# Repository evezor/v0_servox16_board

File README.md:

# Servo x16 Board
*please note this board has been deprecated.

This board uses the Evezor Stamp STMF405 MCU

source: https://github.com/evezor/Evezor-Stamp-STMF405

An edge board containing a PCA9685 driver chip capable of controlling 16 servos or LEDs. The board also contains 2 pushbuttons and a dpad for easy control/ debugging. 
Servo power must be supplied from external source

source files can be found here: https://github.com/evezor/v0_servox16_board

Evezor® and all associated marks, logos, and designs are registered trademarks and protected by copyright. Unauthorized use or reproduction of these trademarks and copyrighted materials is strictly prohibited.

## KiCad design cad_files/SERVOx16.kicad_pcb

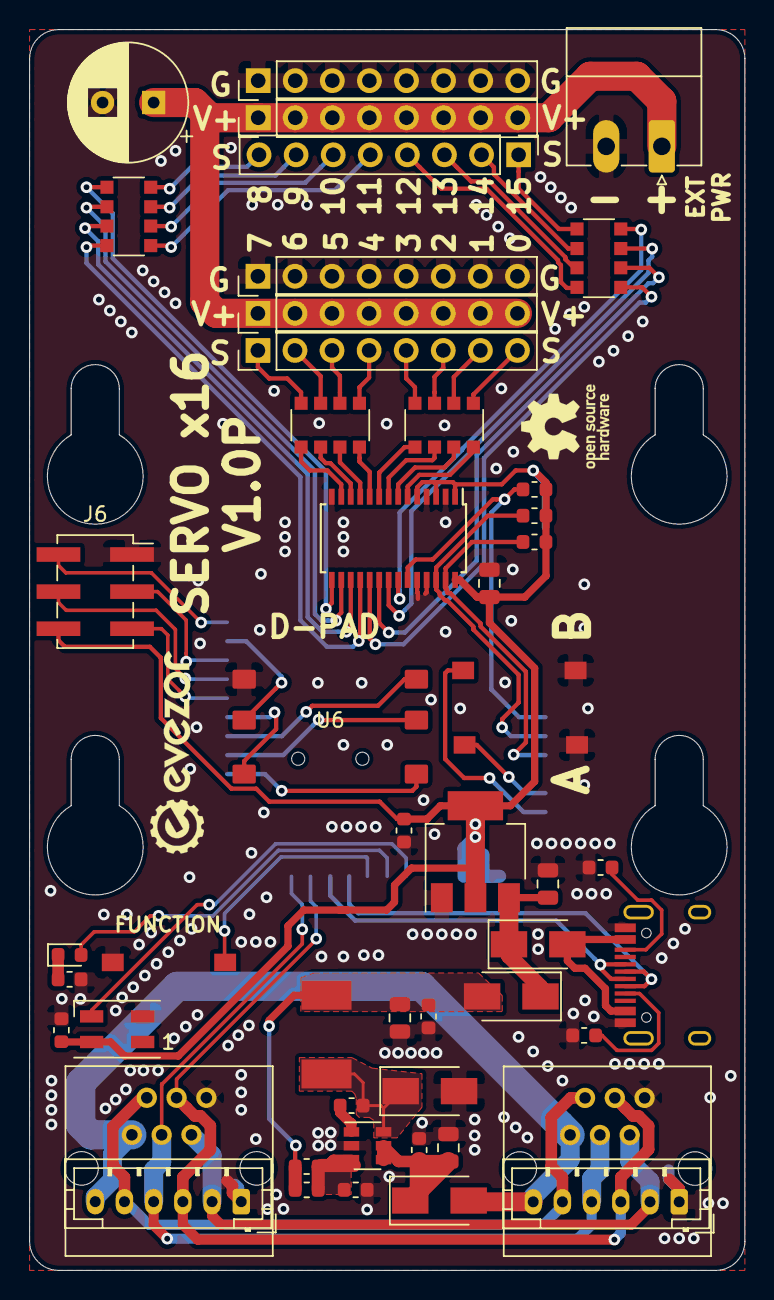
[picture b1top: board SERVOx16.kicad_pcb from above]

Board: 2 copper layers, 49.0 x 85.0 mm, 51 parts (1 on the bottom side), 69 nets.

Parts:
C1, C2, C3, C5, C10: .1uF; C_0603_1608Metric
C4: 4.7uF; C_0805_2012Metric
C6: 22uF; C_0805_2012Metric
C8, C11: 10uF; C_0805_2012Metric
C9: C_Small; C_0603_1608Metric
C12: CP; CP_Radial_D8.0mm_P3.50mm
D1, D2, D4, D5: SX35_SCHOTTKY; D_SMA
D3: LED; LED_0603_1608Metric
D6: SK6812MINI; LED_SK6812MINI_PLCC4_3.5x3.5mm_P1.75mm
J1: USB_C_Receptacle_USB2.0; USB_C_Receptacle_HRO_TYPE-C-31-M-12
J2, J3: RJ11; RJ11_C189747_Horizontal
J4, J5: PH; JST_PH_B6B-PH-K_1x06_P2.00mm_Vertical
J6: Conn_02x03_Odd_Even; PinSocket_2x03_P2.54mm_Vertical_SMD
J7: Conn_01x02; PhoenixContact_MC_1,5_2-G-3.81_1x02_P3.81mm_Horizontal
J8, J9, J10, J11, J12, J13: Conn_01x08; PinHeader_1x08_P2.54mm_Vertical
L1: 22uH; INDUCTOR_7.5X6.6_GCDA0630-220MC
R1, R5: 15k; R_0603_1608Metric
R2: 82k; R_0603_1608Metric
R3, R4: 5.1k; R_0603_1608Metric
R8: 10k; R_0603_1608Metric
R9, R10: 4.7k; R_0603_1608Metric
RN1, RN2, RN3: R_Pack04; R_Array_Convex_4x1206
RN4: 220x4; R_Array_Convex_4x1206
SW1, SW2, SW3: SW_Push; SWITCH_2x3_SMD_TACTILE_GREEN
U1: SY8401ABC; SOT-23-6
U2: AMS1117-3.3; SOT-223-3_TabPin2
U3: EDGE_STM32F405_CPU_V1; EDGE_STAMP
U5: PCA9685PW; TSSOP-28_4.4x9.7mm_P0.65mm
U6: SWITCH_5-WAY_TACTIL_10X10; SWITCH_5WAY_10x10

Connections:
+3V3: C9.2, C10.1, C11.1, D6.4, J6.6, R8.1, R9.1, R10.1, U2.2, U3.1, U3.18, U5.1, U5.3, U5.5, U5.28
/BOOT: J6.3, U3.36
/BUTTON_A: SW3.1, U3.15
/BUTTON_B: SW2.1, U3.16
/CAN_H: J2.3, J3.3, J4.3, J5.3, U3.26
/CAN_L: J2.4, J3.4, J4.4, J5.4, U3.27
/CC1: J1.A5, R4.1
/CC2: J1.B5, R3.1
/D+: J1.A6, J1.B6, U3.25
/D-: J1.A7, J1.B7, U3.24
/DOWN: U3.30, U6.6
/FD_H: J2.2, J3.2, J4.2, J5.2
/FD_L: J2.5, J3.5, J4.5, J5.5
/FUNCTION_BUTTON: SW1.1, U3.23
/HBT_LED: D3.2, U3.22
/LEFT: U3.37, U6.2
/NEO_STATUS: D6.3, U3.21
/OE: R8.2, U3.11, U5.23
/OUTPUT_0: J12.8, RN1.1
/OUTPUT_1: J12.7, RN1.2
/OUTPUT_2: J12.6, RN1.3
/OUTPUT_3: J12.5, RN1.4
/OUTPUT_4: J12.4, RN2.1
/OUTPUT_5: J12.3, RN2.2
/OUTPUT_6: J12.2, RN2.3
/OUTPUT_7: J12.1, RN2.4
/OUTPUT_8: J8.8, RN3.8
/OUTPUT_9: J8.7, RN3.7
/OUTPUT_10: J8.6, RN3.6
/OUTPUT_11: J8.5, RN3.5
/OUTPUT_12: J8.4, RN4.8
/OUTPUT_13: J8.3, RN4.7
/OUTPUT_14: J8.2, RN4.6
/OUTPUT_15: J8.1, RN4.5
/PUSH: U3.33, U6.3
/RESET: J6.2, U3.38
/RIGHT: U3.31, U6.5
/SCL: R10.2, U3.12, U5.26
/SDA: R9.2, U3.13, U5.27
/SLEEVE_SCL: J6.5, U3.34
/SLEEVE_SDA: J6.4, U3.35
/UP: U3.32, U6.4
/USB_VCC: D4.2, J1.A4, J1.A9, J1.B4, J1.B9
/VREG_OUT: C2.1, C5.1, C6.1, D5.2, L1.2, R2.1
GND: C3.2, C4.2, C5.2, C6.2, C8.2, C9.1, C10.2, C11.2, C12.2, D1.2, D6.2, J1.A1, J1.A12, J1.B1, J1.B12, J2.1, J3.1, J4.1, J5.1, J6.1, J7.2, J9.1, J9.2, J9.3, J9.4, J9.5, J9.6, J9.7, J9.8, J11.1, J11.2, J11.3, J11.4, J11.5, J11.6, J11.7, J11.8, R1.1, R3.2, R4.2, R5.1, SW1.2, SW2.2, SW3.2, U1.2, U2.1, U3.2, U3.17, U3.43, U5.2, U5.4, U5.14, U5.24, U5.25, U6.1
unnamed: C1.1, D1.1, L1.1, U1.6
unnamed: C1.2, U1.1
unnamed: C2.2, R1.2, R2.2, U1.3
unnamed: C3.1, C4.1, D2.1, U1.4, U1.5
unnamed: C8.1, D4.1, D5.1, U2.3
unnamed: C12.1, J7.1, J10.1, J10.2, J10.3, J10.4, J10.5, J10.6, J10.7, J10.8, J13.1, J13.2, J13.3, J13.4, J13.5, J13.6, J13.7, J13.8
unnamed: D3.1, R5.2
unnamed: RN1.5, U5.9
unnamed: RN1.6, U5.8
unnamed: RN1.7, U5.7
unnamed: RN1.8, U5.6
unnamed: RN2.5, U5.13
unnamed: RN2.6, U5.12
unnamed: RN2.7, U5.11
unnamed: RN2.8, U5.10
unnamed: RN3.1, U5.15
unnamed: RN3.2, U5.16
unnamed: RN3.3, U5.17
unnamed: RN3.4, U5.18
unnamed: RN4.1, U5.19
unnamed: RN4.2, U5.20
unnamed: RN4.3, U5.21
unnamed: RN4.4, U5.22
VBUS: D2.2, J2.6, J3.6, J4.6, J5.6

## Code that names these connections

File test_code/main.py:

#Servo x16 v1.0p test code

######################
#Notes
#Servos min=650 max=2300
servo_max = 650
servo_min = 2300

from machine import Pin, I2C
from pyb import CAN
import utime
import servo
#import pca9685

print("starting Servo x16 v1.1p test code")
print("v1.0")
print("initializing")
can = CAN(1, CAN.NORMAL)
can.setfilter(0, CAN.LIST16, 0, (123, 124, 125, 126))

#sleep to let pca9685 wake up
utime.sleep_ms(500)
i2c = I2C(2, freq=1000000)


#Setup Pins
HBT_LED = Pin("E8", Pin.OUT)
FUNC_BUTTON = Pin("SD_DETECT", Pin.IN, Pin.PULL_UP) 
NEO_STATUS = Pin("E7", Pin.OUT)

BUTTON_A = Pin("E4", Pin.IN, Pin.PULL_UP)
BUTTON_B = Pin("E5", Pin.IN, Pin.PULL_UP)

UP = Pin("E12", Pin.IN, Pin.PULL_UP)
DOWN = Pin("E10", Pin.IN, Pin.PULL_UP)
LEFT = Pin("E17", Pin.IN, Pin.PULL_UP)
RIGHT = Pin("E11", Pin.IN, Pin.PULL_UP)
DPAD_PUSH = Pin("E13", Pin.IN, Pin.PULL_UP)



#OE pin is the 'enable' pin for the outputs. ACTIVE LOW!
OE = Pin("E2", Pin.OUT)
OE.value(0)

#Setup hbt timer
hbt_state = 0
hbt_interval = 500
start = utime.ticks_ms()
next_hbt = utime.ticks_add(start, hbt_interval)
HBT_LED.value(hbt_state)

#Setup pca9685
#pca = pca9685.PCA9685(i2c)
servos = servo.Servos(i2c)


print("setup complete")


def chk_hbt():
    global next_hbt
    global hbt_state
    now = utime.ticks_ms()
    if utime.ticks_diff(next_hbt, now) <= 0:
        if hbt_state == 1:
            hbt_state = 0
            HBT_LED.value(hbt_state)
            #print("hbt")
        else:
            hbt_state = 1
            HBT_LED.value(hbt_state)  
        
        next_hbt = utime.ticks_add(next_hbt, hbt_interval)

def send():
    can.send('servoX16', 123)   # send a message with id 123
    
def get():
    mess = can.recv(0)
    print(mess)
    simple_test()    

def simple_test():
    move_all(servo_max)
    move_all(servo_min)
    
def move_all(us_delay):
    print("moving all servos to " + str(us_delay))
    for i in range(16):
        servos.position(i, us=us_delay)
        utime.sleep_ms(100)
    print("done")
        
while True:
    chk_hbt()
    if not (FUNC_BUTTON.value()):
        print("function button")
        send()
        simple_test()
        utime.sleep_ms(200)
        
    if not (BUTTON_A.value()):
        print("A button")        
        utime.sleep_ms(200)    

    if not (BUTTON_B.value()):
        print("B button")        
        utime.sleep_ms(200)    

    if not (UP.value()):
        print("UP button")        
        utime.sleep_ms(200)    

    if not (DOWN.value()):
        print("DOWN button")        
        utime.sleep_ms(200)    

    if not (LEFT.value()):
        print("LEFT button")  
        move_all(servo_min)
        utime.sleep_ms(200)    

    if not (RIGHT.value()):
        print("RIGHT button")
        move_all(servo_max)
        utime.sleep_ms(200)    

    if not (DPAD_PUSH.value()):
        print("DPAD_PUSH button")        
        utime.sleep_ms(200)    

    if(can.any(0)):
        get()

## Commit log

2020-12-27 update documentation
2020-12-28 make test code
2023-09-11 Create LICENSE
2023-09-11 add pics
2023-09-11 add more
